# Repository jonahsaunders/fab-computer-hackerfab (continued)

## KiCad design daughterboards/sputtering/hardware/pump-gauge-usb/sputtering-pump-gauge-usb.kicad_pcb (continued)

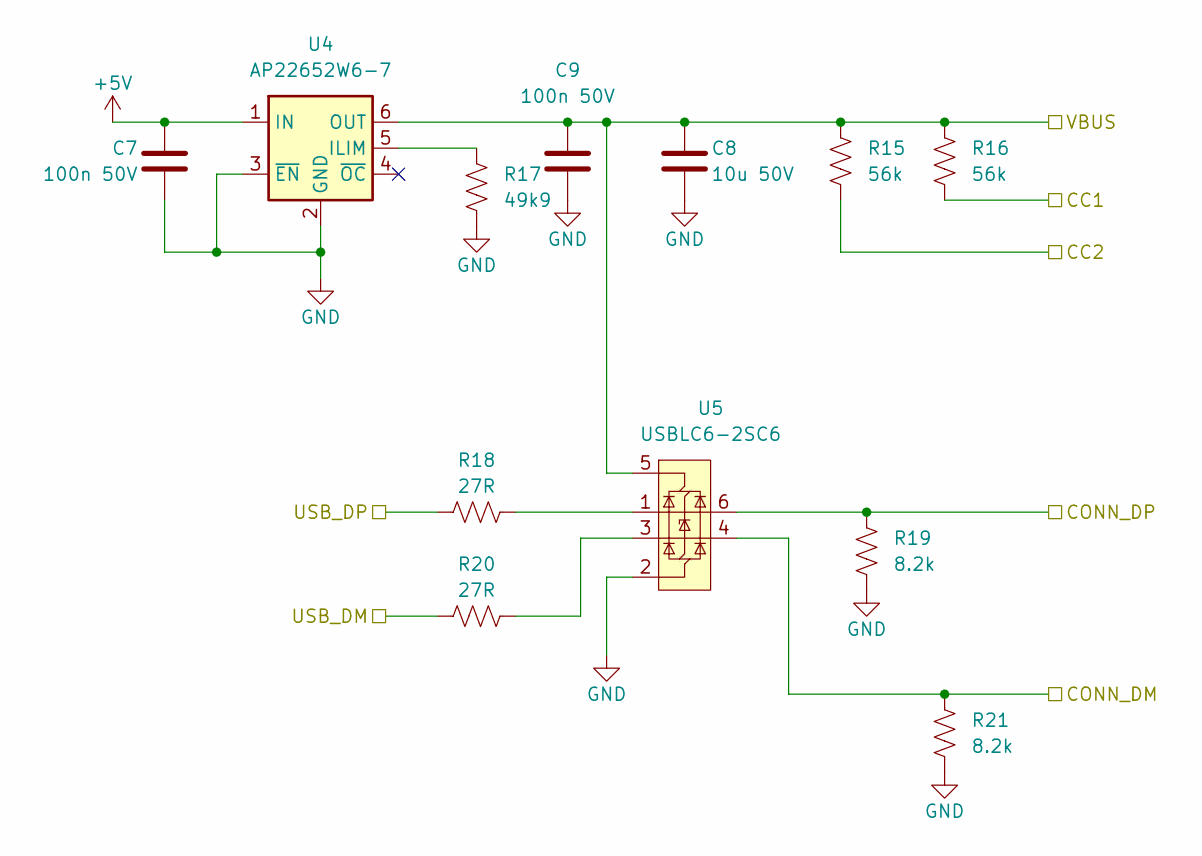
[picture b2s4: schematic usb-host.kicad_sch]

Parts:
C7, C9: 100n 50V; C_0402_1005Metric; LCSC C307331
C8: 10u 50V; C_1206_3216Metric; LCSC C13585
R15, R16: 56k; R_0603_1608Metric; MPN UNI-ROYAL 0603WAF5602T5E; LCSC C23206
R17: 49k9; R_0603_1608Metric; MPN UNI-ROYAL 0603WAF4992T5E; LCSC C23184
R18, R20: 27R; R_0402_1005Metric; LCSC C25100
R19, R21: 8.2k; R_0603_1608Metric; MPN UNI-ROYAL 0603WAF8201T5E; LCSC C25981
U4: AP22652W6-7; SOT-23-6; MPN Diodes AP22652W6-7; LCSC C2158038
U5: USBLC6-2SC6; SOT-23-6; LCSC C7519

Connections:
+5V: C7.1, U4.1 (IN); also elsewhere on the board
/USB_DM: R20.1; also elsewhere on the board
/USB_DP: R18.1; also elsewhere on the board
/usb-host/CC1: R16.2; also elsewhere on the board
/usb-host/CC2: R15.2; also elsewhere on the board
/usb-host/CONN_DM: R21.1, U5.4 (I/O2); also elsewhere on the board
/usb-host/CONN_DP: R19.1, U5.6 (I/O1); also elsewhere on the board
/usb-host/VBUS: C8.1, C9.1, R15.1, R16.1, U4.6 (OUT), U5.5 (VBUS); also elsewhere on the board
GND: C7.2, C8.2, C9.2, R17.2, R19.2, R21.2, U4.2 (GND), U4.3 (~EN), U5.2 (GND); also elsewhere on the board
unnamed: R18.2, U5.1 (I/O1)
unnamed: R20.2, U5.3 (I/O2)
unnamed: R17.1, U4.5 (ILIM)

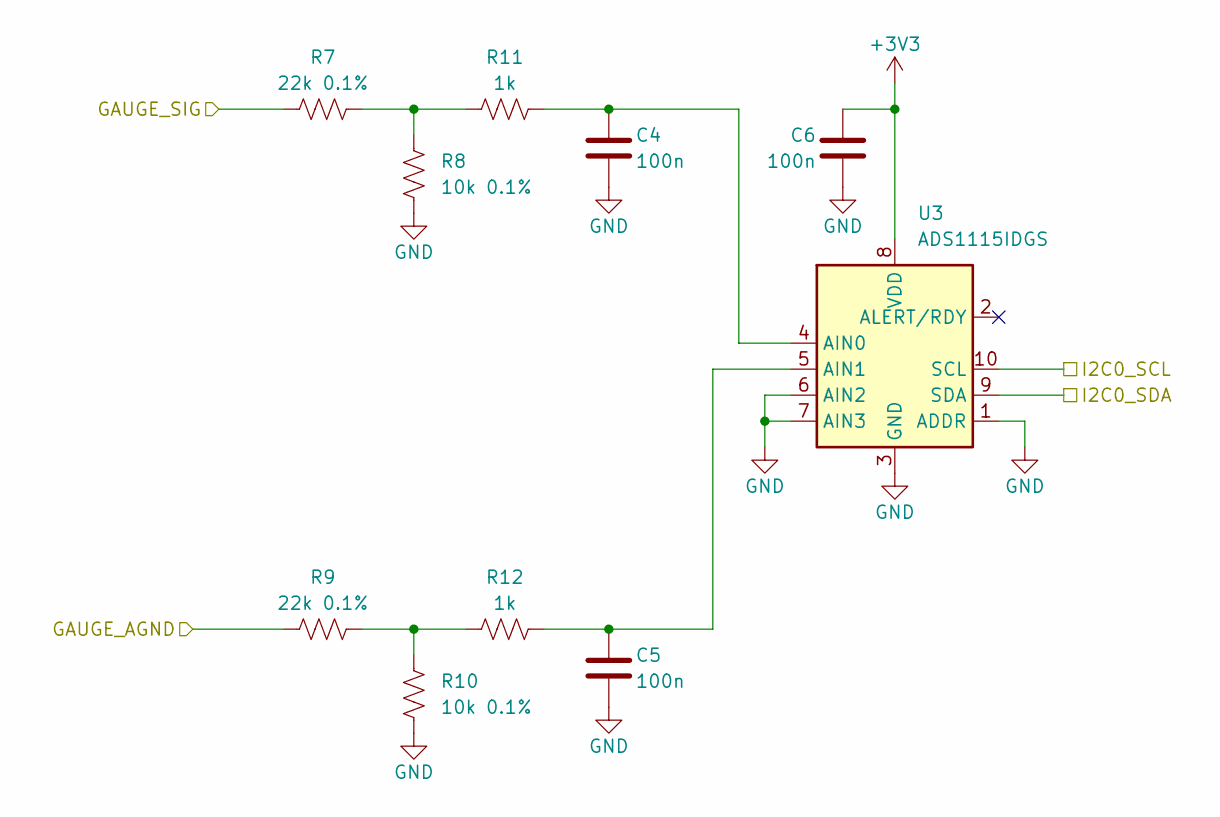
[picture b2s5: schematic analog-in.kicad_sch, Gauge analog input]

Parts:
C4, C5, C6: 100n; C_0402_1005Metric; LCSC C1525
R7, R9: 22k 0.1%; R_0603_1608Metric; MPN Yageo RT0603BRE0722KL; LCSC C705830
R8, R10: 10k 0.1%; R_0603_1608Metric; MPN Yageo RT0603BRE0710KL; LCSC C136139
R11, R12: 1k; R_0603_1608Metric; LCSC C21190
U3: ADS1115IDGS; TSSOP-10_3x3mm_P0.5mm; MPN TI ADS1115IDGSR; LCSC C37593

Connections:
+3V3: C6.1, U3.8 (VDD); also elsewhere on the board
/I2C0_SCL: U3.10 (SCL); also elsewhere on the board
/I2C0_SDA: U3.9 (SDA); also elsewhere on the board
/analog-in/GAUGE_AGND: R9.1; also elsewhere on the board
/analog-in/GAUGE_SIG: R7.1; also elsewhere on the board
GND: C4.2, C5.2, C6.2, R8.2, R10.2, U3.1 (ADDR), U3.3 (GND), U3.6 (AIN2), U3.7 (AIN3); also elsewhere on the board
unnamed: R9.2, R10.1, R12.1
unnamed: R7.2, R8.1, R11.1
unnamed: C4.1, R11.2, U3.4 (AIN0)
unnamed: C5.1, R12.2, U3.5 (AIN1)

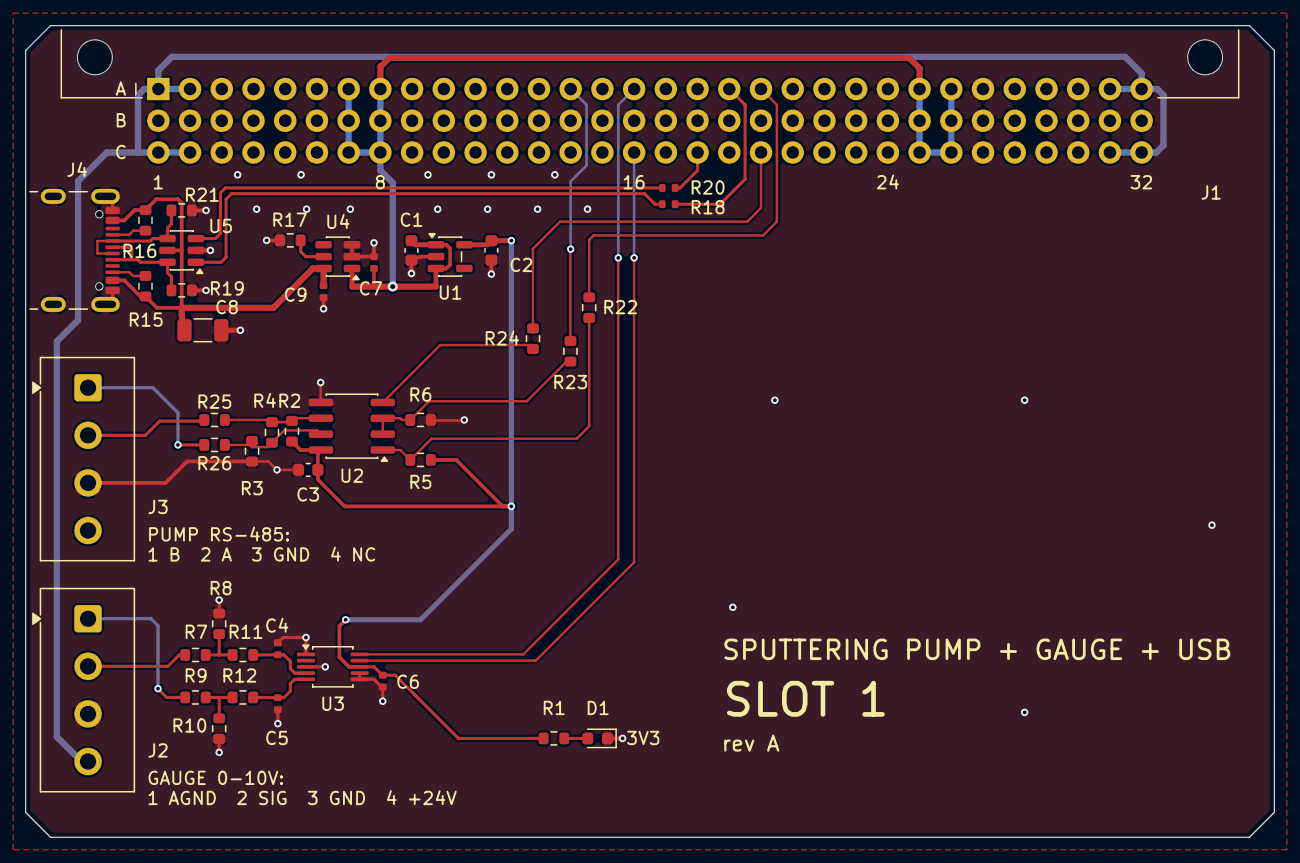
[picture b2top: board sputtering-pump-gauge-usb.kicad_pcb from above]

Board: 2 copper layers, 100.0 x 65.0 mm, 43 parts (0 on the bottom side), 33 nets.

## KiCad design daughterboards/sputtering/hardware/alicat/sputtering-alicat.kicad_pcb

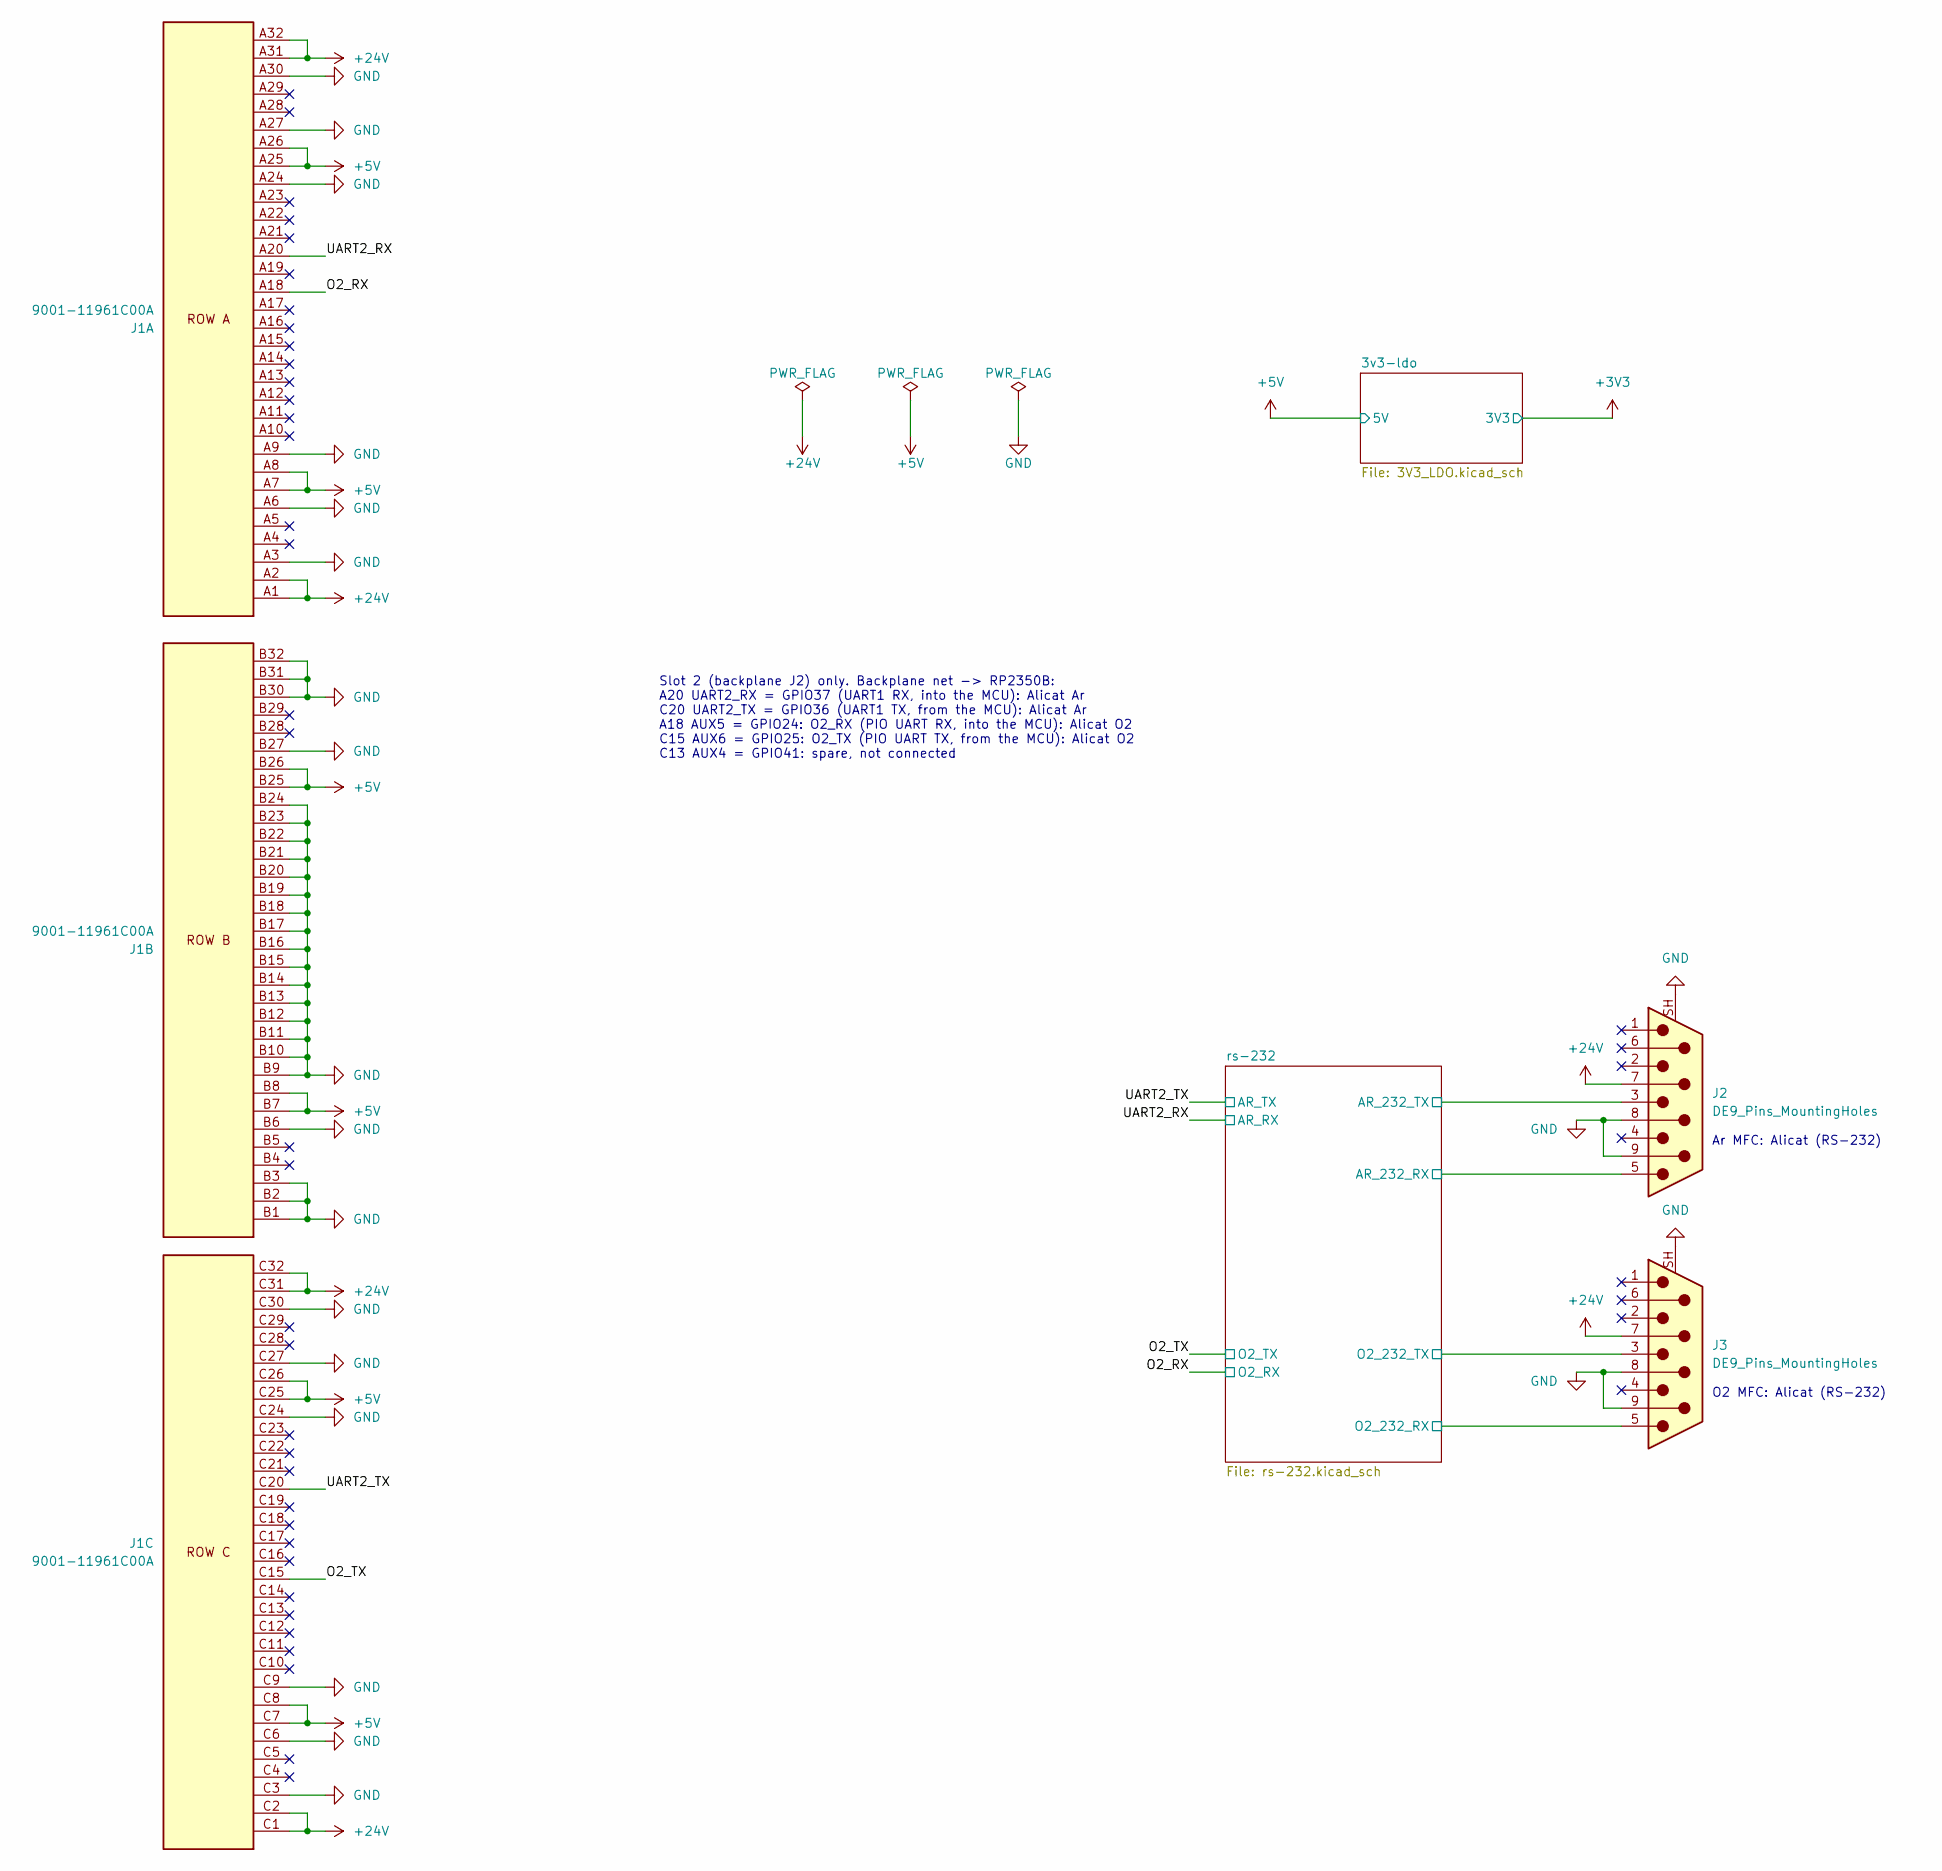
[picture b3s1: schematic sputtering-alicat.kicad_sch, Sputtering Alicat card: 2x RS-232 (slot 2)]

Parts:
J1: 9001-11961C00A; WingTAT_9001-11961C00A_DIN41612_C_3x32_RightAngle; LCSC C5173361
J2, J3: DE9_Pins_MountingHoles; DSUB-9_Pins_Horizontal_P2.77x2.84mm_EdgePinOffset7.70mm_Hou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; MPN CONNFLY DS1037-09MNAKT74-0CC; LCSC C75750

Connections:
+5V: J1.A7, J1.A8, J1.A25, J1.A26, J1.B7, J1.B8, J1.B25, J1.B26, J1.C7, J1.C8, J1.C25, J1.C26; also elsewhere on the board
+24V: J1.A1, J1.A2, J1.A31, J1.A32, J1.C1, J1.C2, J1.C31, J1.C32, J2.7, J3.7
/O2_RX: J1.A18; also elsewhere on the board
/O2_TX: J1.C15; also elsewhere on the board
/UART2_RX: J1.A20; also elsewhere on the board
/UART2_TX: J1.C20; also elsewhere on the board
/rs-232/AR_232_RX: J2.5; also elsewhere on the board
/rs-232/AR_232_TX: J2.3; also elsewhere on the board
/rs-232/O2_232_RX: J3.5; also elsewhere on the board
/rs-232/O2_232_TX: J3.3; also elsewhere on the board
GND: J1.A3, J1.A6, J1.A9, J1.A24, J1.A27, J1.A30, J1.B1, J1.B2, J1.B3, J1.B6, J1.B9, J1.B10, J1.B11, J1.B12, J1.B13, J1.B14, J1.B15, J1.B16, J1.B17, J1.B18, J1.B19, J1.B20, J1.B21, J1.B22, J1.B23, J1.B24, J1.B27, J1.B30, J1.B31, J1.B32, J1.C3, J1.C6, J1.C9, J1.C24, J1.C27, J1.C30, J2.8, J2.9, J2.SH (PAD), J3.8, J3.9, J3.SH (PAD); also elsewhere on the board

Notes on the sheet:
Ar MFC: Alicat (RS-232)
Slot 2 (backplane J2) only. Backplane net -> RP2350B: A20 UART2_RX = GPIO37 (UART1 RX, into the MCU): Alicat Ar C20 UART2_TX = GPIO36 (UART1 TX, from the MCU): Alicat Ar A18 AUX5 = GPIO24: O2_RX (PIO UART RX, into the MCU): Alicat O2 C15 AUX6 = GPIO25: O2_TX (PIO UART TX, from the MCU): Alicat O2 C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
O2 MFC: Alicat (RS-232)

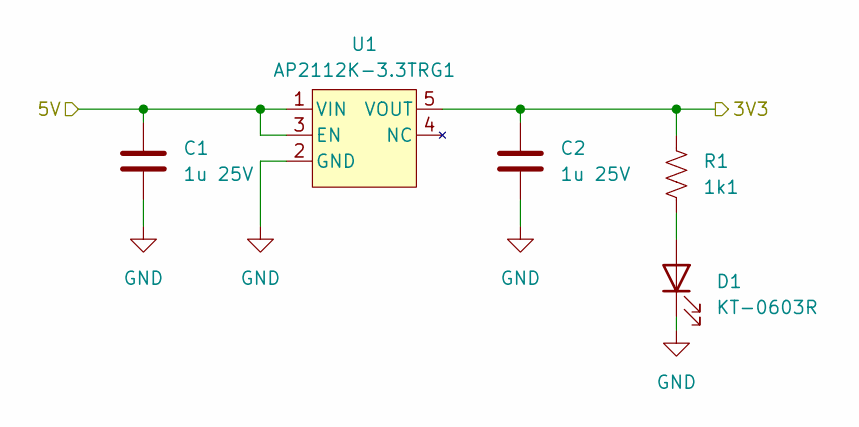
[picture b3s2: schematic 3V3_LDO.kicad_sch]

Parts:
C1, C2: 1u 25V; C_0603_1608Metric; LCSC C15849
D1: KT-0603R; LED_0603_1608Metric; MPN KT-0603R; LCSC C2286
R1: 1k1; R_0603_1608Metric; LCSC C22764
U1: AP2112K-3.3TRG1; SOT-23-5; LCSC C51118

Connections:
+3V3: C2.1, R1.1, U1.5 (VOUT); also elsewhere on the board
+5V: C1.1, U1.1 (VIN), U1.3 (EN); also elsewhere on the board
GND: C1.2, C2.2, D1.1 (K), U1.2 (GND); also elsewhere on the board
unnamed: D1.2 (A), R1.2

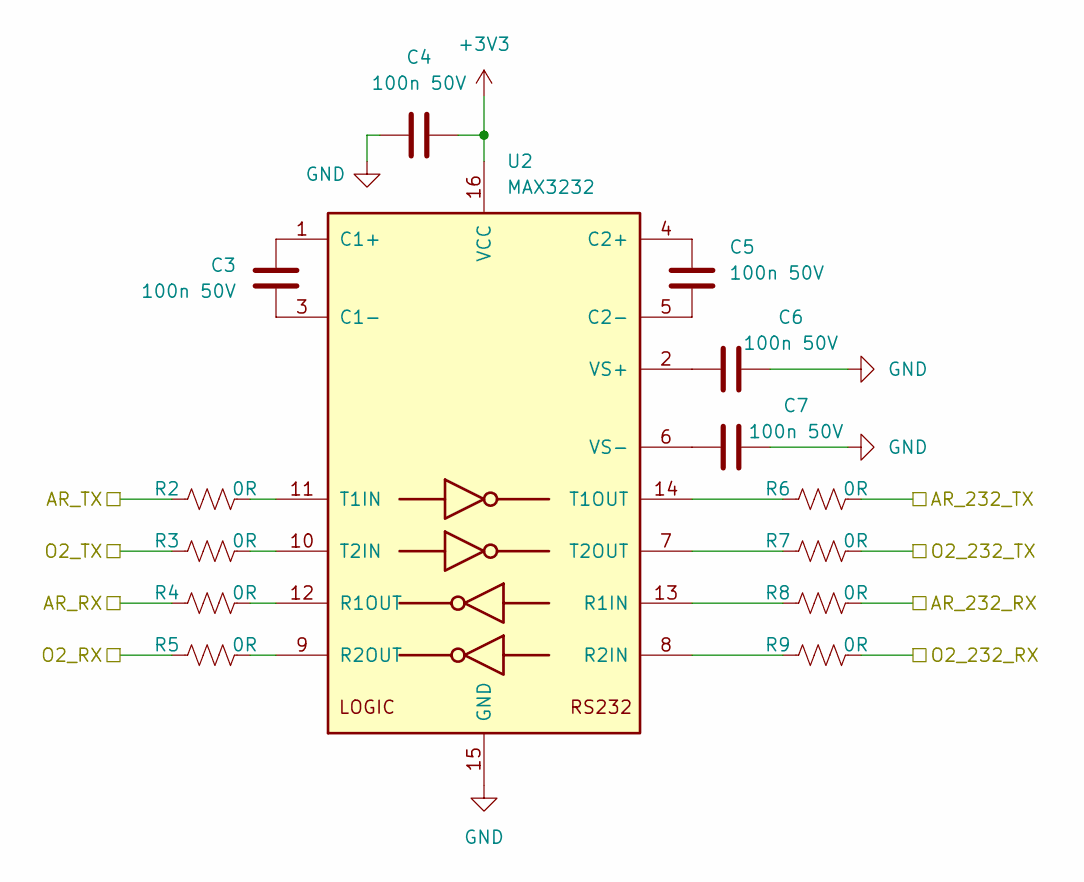
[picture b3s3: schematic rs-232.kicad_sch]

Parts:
C3, C4, C5, C6, C7: 100n 50V; C_0402_1005Metric; LCSC C307331
R2, R3, R4, R5, R6, R7, R8, R9: 0R; R_0603_1608Metric; LCSC C21189
U2: MAX3232; SOIC-16_3.9x9.9mm_P1.27mm; MPN Maxim MAX3232ESE+T; LCSC C15846

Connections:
+3V3: C4.1, U2.16 (VCC); also elsewhere on the board
/O2_RX: R5.1; also elsewhere on the board
/O2_TX: R3.1; also elsewhere on the board
/UART2_RX: R4.1; also elsewhere on the board
/UART2_TX: R2.1; also elsewhere on the board
/rs-232/AR_232_RX: R8.2; also elsewhere on the board
/rs-232/AR_232_TX: R6.2; also elsewhere on the board
/rs-232/O2_232_RX: R9.2; also elsewhere on the board
/rs-232/O2_232_TX: R7.2; also elsewhere on the board
GND: C4.2, C6.1, C7.1, U2.15 (GND); also elsewhere on the board
unnamed: C3.2, U2.1 (C1+)
unnamed: C3.1, U2.3 (C1-)
unnamed: C5.2, U2.4 (C2+)
unnamed: C5.1, U2.5 (C2-)
unnamed: R8.1, U2.13 (R1IN)
unnamed: R4.2, U2.12 (R1OUT)
unnamed: R9.1, U2.8 (R2IN)
unnamed: R5.2, U2.9 (R2OUT)
unnamed: R2.2, U2.11 (T1IN)
unnamed: R6.1, U2.14 (T1OUT)
unnamed: R3.2, U2.10 (T2IN)
unnamed: R7.1, U2.7 (T2OUT)
unnamed: C6.2, U2.2 (VS+)
unnamed: C7.2, U2.6 (VS-)

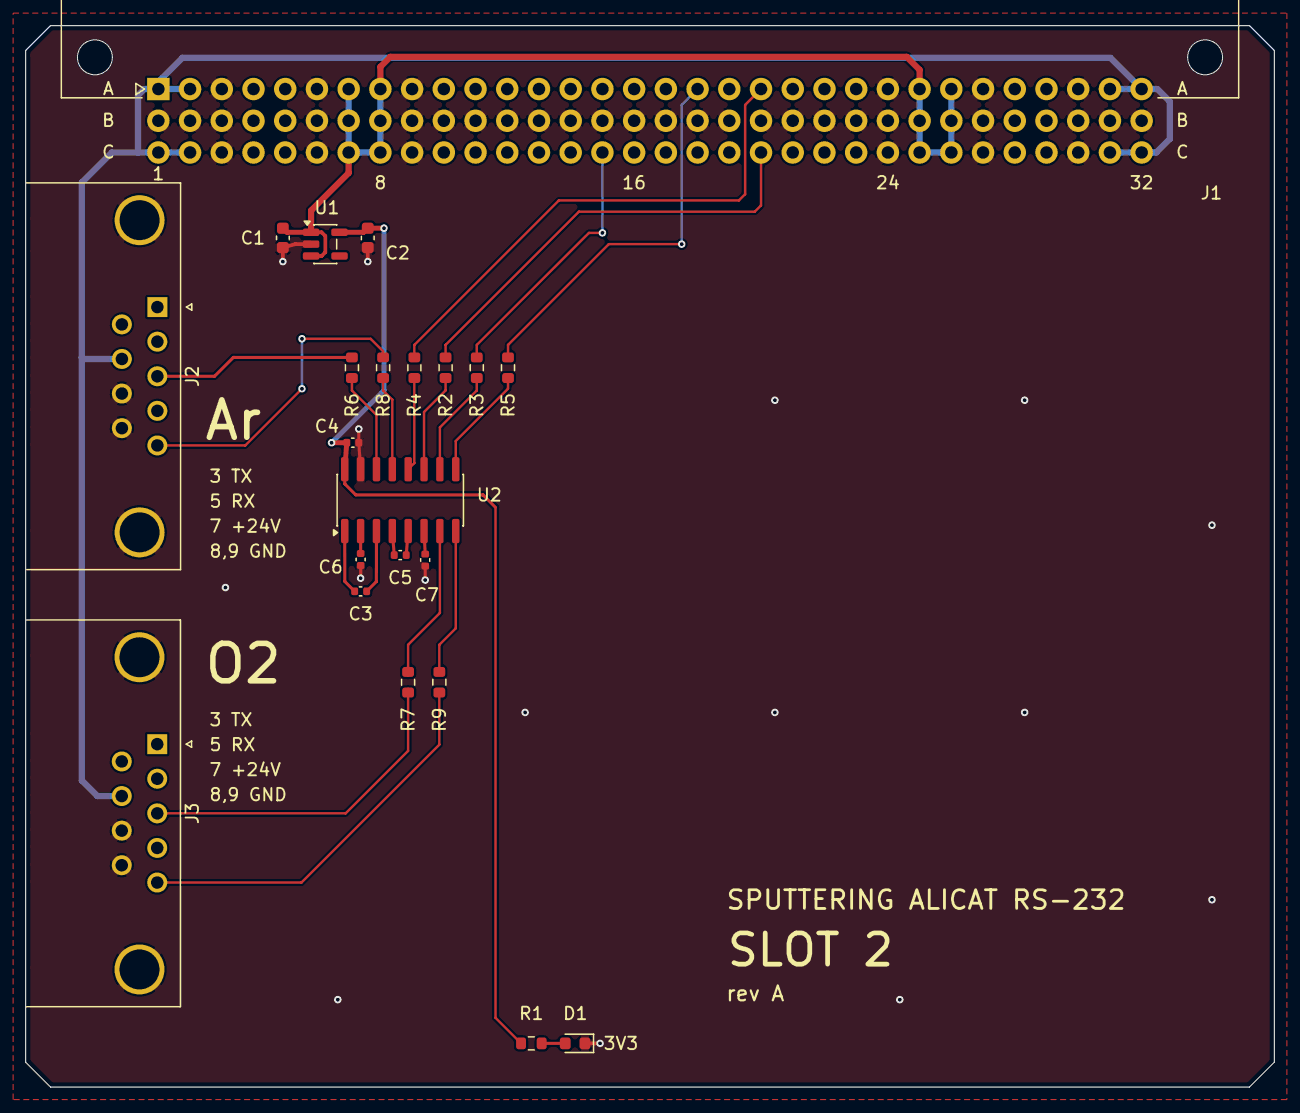
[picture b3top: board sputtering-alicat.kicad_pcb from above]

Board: 2 copper layers, 100.0 x 85.0 mm, 22 parts (0 on the bottom side), 27 nets.

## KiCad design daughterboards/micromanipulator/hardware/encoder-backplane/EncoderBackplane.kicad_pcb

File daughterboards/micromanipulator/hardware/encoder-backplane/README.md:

# Slot-mounted encoder splitter

Open [EncoderBackplane.kicad_pro](EncoderBackplane.kicad_pro) in KiCad 10. This **100 × 26 mm, four-layer** card plugs into an unused backplane slot and connects three existing XYZ magnetic-encoder boards. Keep the sibling `libraries` directory with it.

The motion card reads the encoders through the existing shared SPI0 bus. The host CPU must leave GPIO16–21 as inputs without pulls; SPI0 and all three selects are reserved for this pair. The host board is unchanged. See the [bus map and requirements](../../docs/backplane-encoder-bus.md).

J1/J2/J3 are JST B6B-PH-K-S(LF)(SN), **LCSC C131342**, matching the original PH6 sensor wiring: 1 GND, 2 CS, 3 SCK, 4 MOSI, 5 MISO, 6 3.3 V. Top-entry plugs project from the component face; the connectors sit at the exposed edge. Local KiCad models show their direction and nominal bodies.

J4 is the same DIN96 male right-angle interface as the motion card. An AP2112M-3.3 uses backplane 5 V; no extra contact or development module is used. TP1/TP2 probe 5 V/3.3 V, with TP3/TP4 grounds. All are 0.8 mm surface copper pads without holes or paste. Eleven fitted parts plus four bare probe pads.

[Schematic PDF](../../docs/encoder-backplane-schematic.pdf) · [3D view](../../docs/encoder-backplane.png) · [BOM](../../docs/encoder-backplane-bom.csv) · [Validation](../../docs/validation.md)

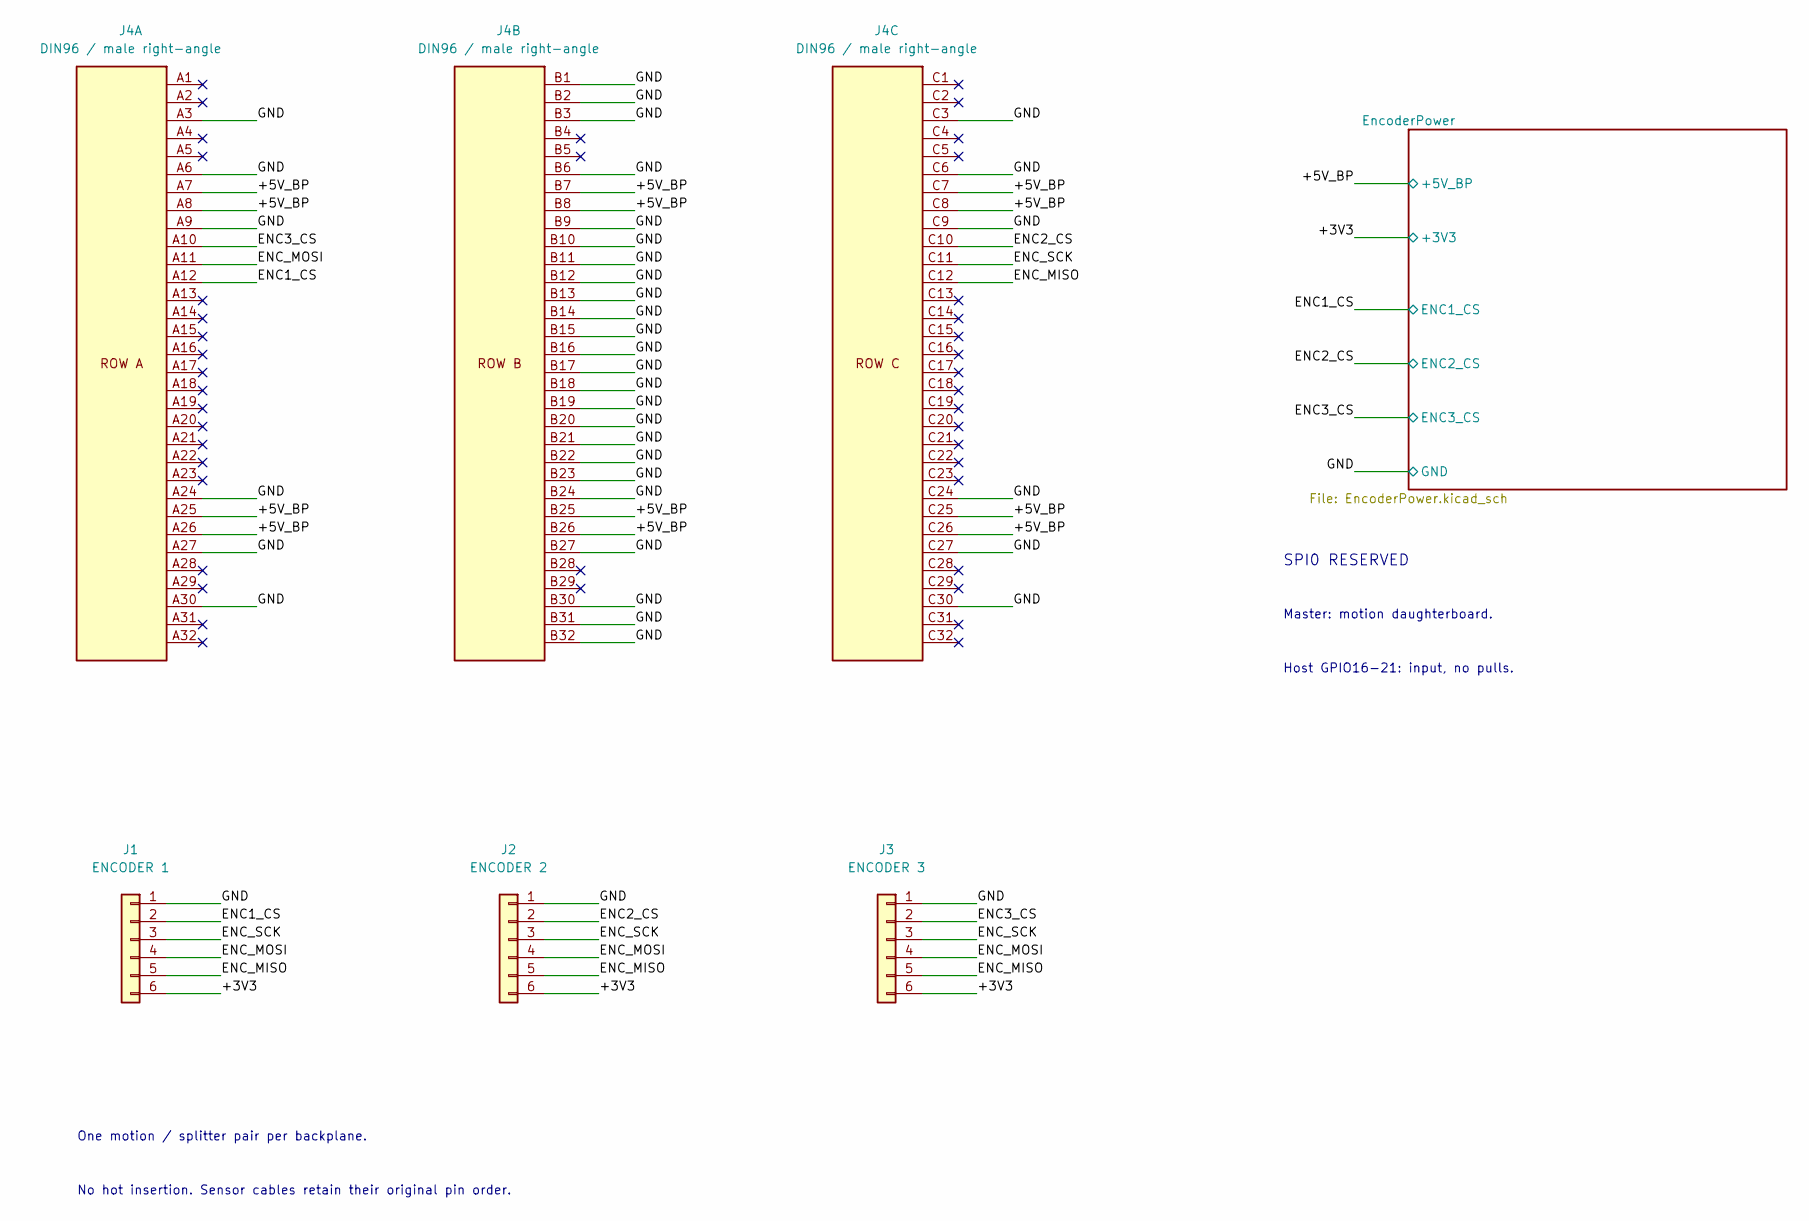
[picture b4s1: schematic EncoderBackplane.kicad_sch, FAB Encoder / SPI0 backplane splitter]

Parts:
J1: ENCODER 1; JST_PH_B6B-PH-K_1x06_P2.00mm_Vertical; MPN B6B-PH-K-S(LF)(SN); LCSC C131342
J2: ENCODER 2; JST_PH_B6B-PH-K_1x06_P2.00mm_Vertical; MPN B6B-PH-K-S(LF)(SN); LCSC C131342
J3: ENCODER 3; JST_PH_B6B-PH-K_1x06_P2.00mm_Vertical; MPN B6B-PH-K-S(LF)(SN); LCSC C131342
J4: DIN96 / male right-angle; DIN96_Male_Horizontal; MPN 9001-11961C00A; LCSC C5173361

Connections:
+3V3: J1.6, J2.6, J3.6; also elsewhere on the board
+5V_BP: J4.A7, J4.A8, J4.A25, J4.A26, J4.B7, J4.B8, J4.B25, J4.B26, J4.C7, J4.C8, J4.C25, J4.C26; also elsewhere on the board
/ENC1_CS: J1.2, J4.A12; also elsewhere on the board
/ENC2_CS: J2.2, J4.C10; also elsewhere on the board
/ENC3_CS: J3.2, J4.A10; also elsewhere on the board
/ENC_MISO: J1.5, J2.5, J3.5, J4.C12
/ENC_MOSI: J1.4, J2.4, J3.4, J4.A11
/ENC_SCK: J1.3, J2.3, J3.3, J4.C11
GND: J1.1, J2.1, J3.1, J4.A3, J4.A6, J4.A9, J4.A24, J4.A27, J4.A30, J4.B1, J4.B2, J4.B3, J4.B6, J4.B9, J4.B10, J4.B11, J4.B12, J4.B13, J4.B14, J4.B15, J4.B16, J4.B17, J4.B18, J4.B19, J4.B20, J4.B21, J4.B22, J4.B23, J4.B24, J4.B27, J4.B30, J4.B31, J4.B32, J4.C3, J4.C6, J4.C9, J4.C24, J4.C27, J4.C30; also elsewhere on the board

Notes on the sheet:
SPI0 RESERVED
Master: motion daughterboard.
Host GPIO16-21: input, no pulls.
One motion / splitter pair per backplane.
No hot insertion. Sensor cables retain their original pin order.

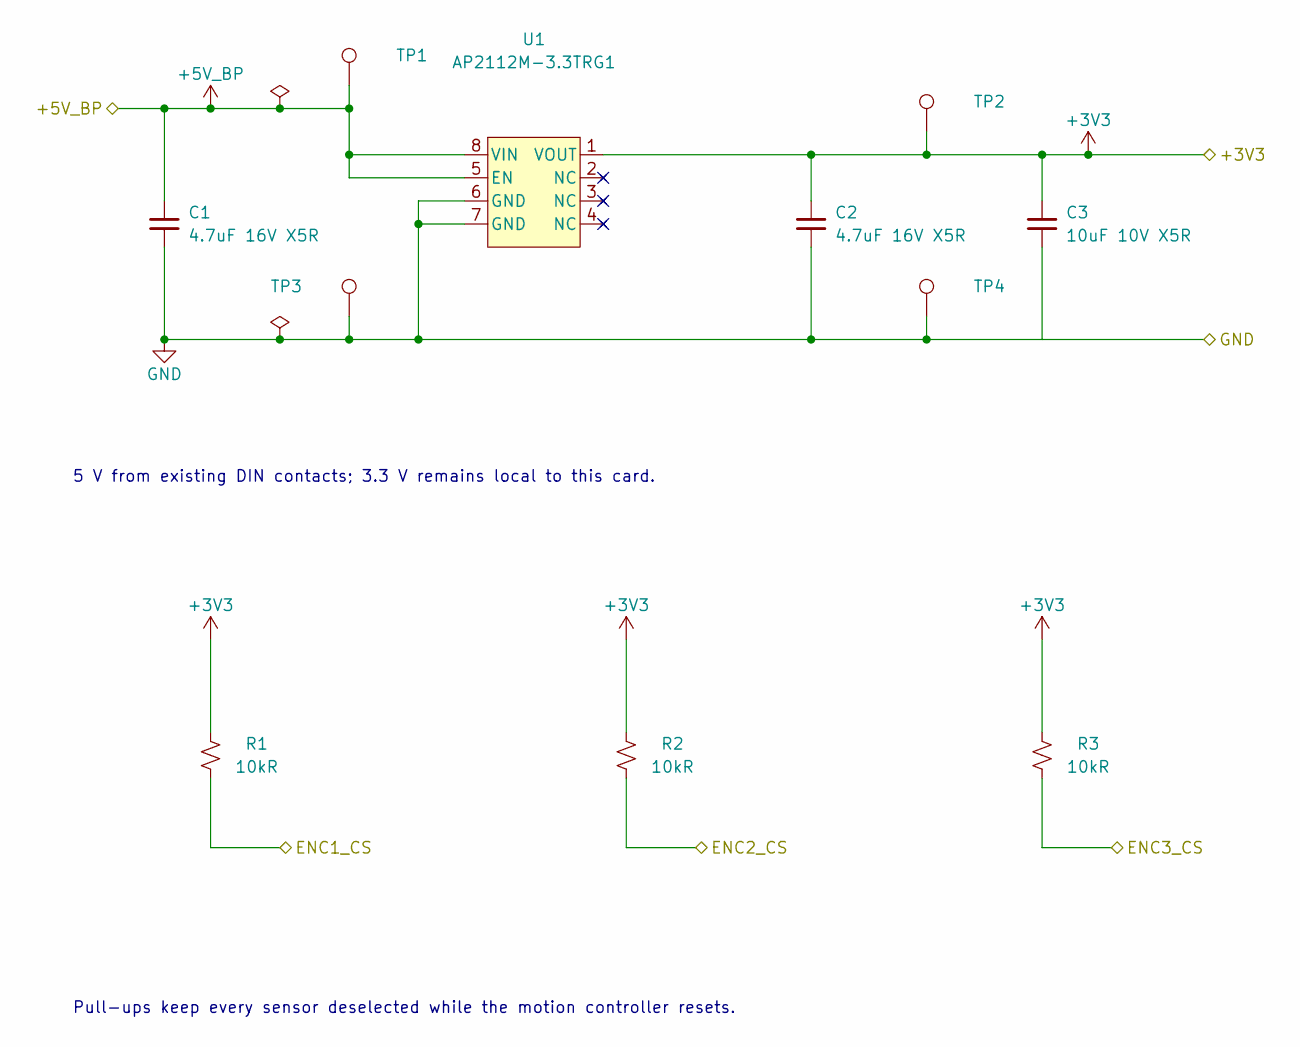
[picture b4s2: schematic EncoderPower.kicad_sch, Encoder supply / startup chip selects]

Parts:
C1, C2: 4.7uF 16V X5R; C_0603_1608Metric; MPN CL10A475KO8NNNC; LCSC C19666
C3: 10uF 10V X5R; C_0603_1608Metric; MPN CL10A106KP8NNNC; LCSC C19702
R1, R2, R3: 10kR; R_0603_1608Metric; MPN 0603WAF1002T5E; LCSC C25804
TP1: 5V; TestPoint_Pad_D0.8mm
TP2: 3V3; TestPoint_Pad_D0.8mm
TP3, TP4: GND; TestPoint_Pad_D0.8mm
U1: AP2112M-3.3TRG1; SOIC-8_3.9x4.9mm_P1.27mm; MPN AP2112M-3.3TRG1; LCSC C5290219

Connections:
+3V3: C2.1, C3.1, R1.2, R2.2, R3.2, TP2.1, U1.1 (VOUT); also elsewhere on the board
+5V_BP: C1.1, TP1.1, U1.5 (EN), U1.8 (VIN); also elsewhere on the board
/ENC1_CS: R1.1; also elsewhere on the board
/ENC2_CS: R2.1; also elsewhere on the board
/ENC3_CS: R3.1; also elsewhere on the board
GND: C1.2, C2.2, C3.2, TP3.1, TP4.1, U1.6 (GND), U1.7 (GND); also elsewhere on the board

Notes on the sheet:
5 V from existing DIN contacts; 3.3 V remains local to this card.
Pull-ups keep every sensor deselected while the motion controller resets.

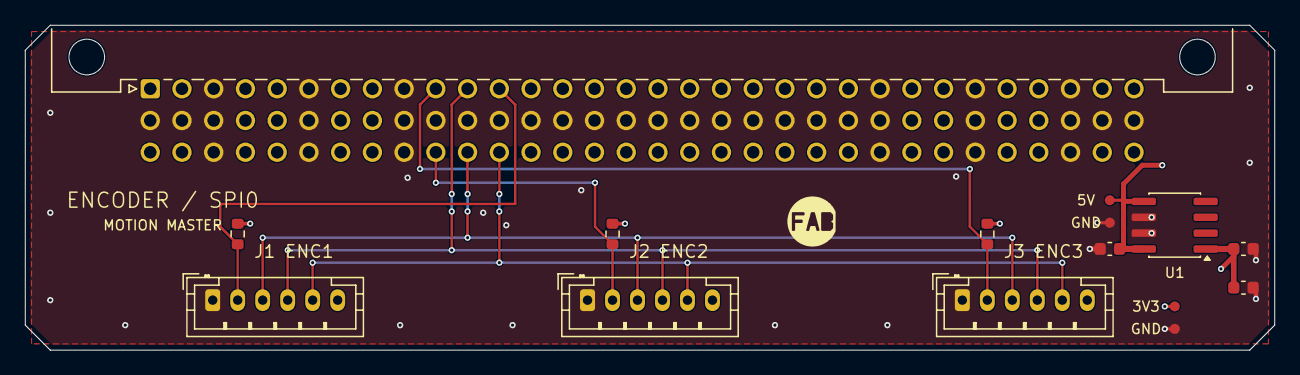
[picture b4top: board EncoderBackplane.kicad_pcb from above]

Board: 4 copper layers, 100.0 x 26.0 mm, 15 parts (0 on the bottom side), 9 nets.

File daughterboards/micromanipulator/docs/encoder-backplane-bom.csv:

Reference,Value,Footprint,Manufacturer part number,Manufacturer,LCSC,Quantity,Procurement status
J1,ENCODER 1,Connector_JST:JST_PH_B6B-PH-K_1x06_P2.00mm_Vertical,B6B-PH-K-S(LF)(SN),JST,C131342,1,Catalog part identified; confirm assembly availability when ordering
J2,ENCODER 2,Connector_JST:JST_PH_B6B-PH-K_1x06_P2.00mm_Vertical,B6B-PH-K-S(LF)(SN),JST,C131342,1,Catalog part identified; confirm assembly availability when ordering
J3,ENCODER 3,Connector_JST:JST_PH_B6B-PH-K_1x06_P2.00mm_Vertical,B6B-PH-K-S(LF)(SN),JST,C131342,1,Catalog part identified; confirm assembly availability when ordering
J4,DIN96 / male right-angle,FabNano:DIN96_Male_Horizontal,9001-11961C00A,WingTAT,C5173361,1,Catalog part identified; confirm assembly availability when ordering
C1,4.7uF 16V X5R,Capacitor_SMD:C_0603_1608Metric,CL10A475KO8NNNC,Samsung Electro-Mechanics,C19666,1,Catalog part identified; confirm assembly availability when ordering
C2,4.7uF 16V X5R,Capacitor_SMD:C_0603_1608Metric,CL10A475KO8NNNC,Samsung Electro-Mechanics,C19666,1,Catalog part identified; confirm assembly availability when ordering
C3,10uF 10V X5R,Capacitor_SMD:C_0603_1608Metric,CL10A106KP8NNNC,Samsung Electro-Mechanics,C19702,1,Catalog part identified; confirm assembly availability when ordering
R1,10kR,Resistor_SMD:R_0603_1608Metric,0603WAF1002T5E,Uniroyal Electronics,C25804,1,Catalog part identified; confirm assembly availability when ordering
R2,10kR,Resistor_SMD:R_0603_1608Metric,0603WAF1002T5E,Uniroyal Electronics,C25804,1,Catalog part identified; confirm assembly availability when ordering
R3,10kR,Resistor_SMD:R_0603_1608Metric,0603WAF1002T5E,Uniroyal Electronics,C25804,1,Catalog part identified; confirm assembly availability when ordering
U1,AP2112M-3.3TRG1,Package_SO:SOIC-8_3.9x4.9mm_P1.27mm,AP2112M-3.3TRG1,Diodes Incorporated,C5290219,1,Catalog part identified; confirm assembly availability when ordering

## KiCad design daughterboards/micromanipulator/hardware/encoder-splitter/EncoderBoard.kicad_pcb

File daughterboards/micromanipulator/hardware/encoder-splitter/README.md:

# Original splitter — source reference only

The active design is now the [slot-mounted encoder card](../encoder-backplane/). This original 36 × 36 mm PH8-to-three-PH6 project is retained for provenance and sensor pinout comparison. Its PH8 connector is not used by the current motion card, which no longer has J6.

# Original XYZ SPI splitter

Open `EncoderBoard.kicad_pro` in KiCad 10. This is HackerFab's existing 36 × 36 mm passive breakout: one PH8 input (J4) and three PH6 outputs (J1–J3). Connect daughterboard J6 to J4 pin-for-pin. The board carries no encoder ICs or development modules.

See the [pin table and import review](../../docs/probe-and-label-review.md#included-original-spi-splitter). Connector positions, pinout, copper and outline are retained from [MicroManipulatorStepper](https://github.com/hacker-fab/MicroManipulatorStepper/tree/fa9a1f8e6d5365c6d5d5f31054d4f2c95aff8f6a/electronics). Models and footprints resolve within the micromanipulator folder. KiCad's standard symbol libraries are used for editing; the schematic contains its cached symbols.

Only local library/model paths, empty datasheet metadata, the daughterboard J6 caption and ERC annotations were normalized. Both ERC and DRC/parity pass. Mounting pads remain electrically isolated as upstream. The original DIYLC distribution drawing is included alongside the KiCad files. Attribution and terms are in [the retained MIT license](../../licenses/MicroManipulatorStepper-MIT.txt).

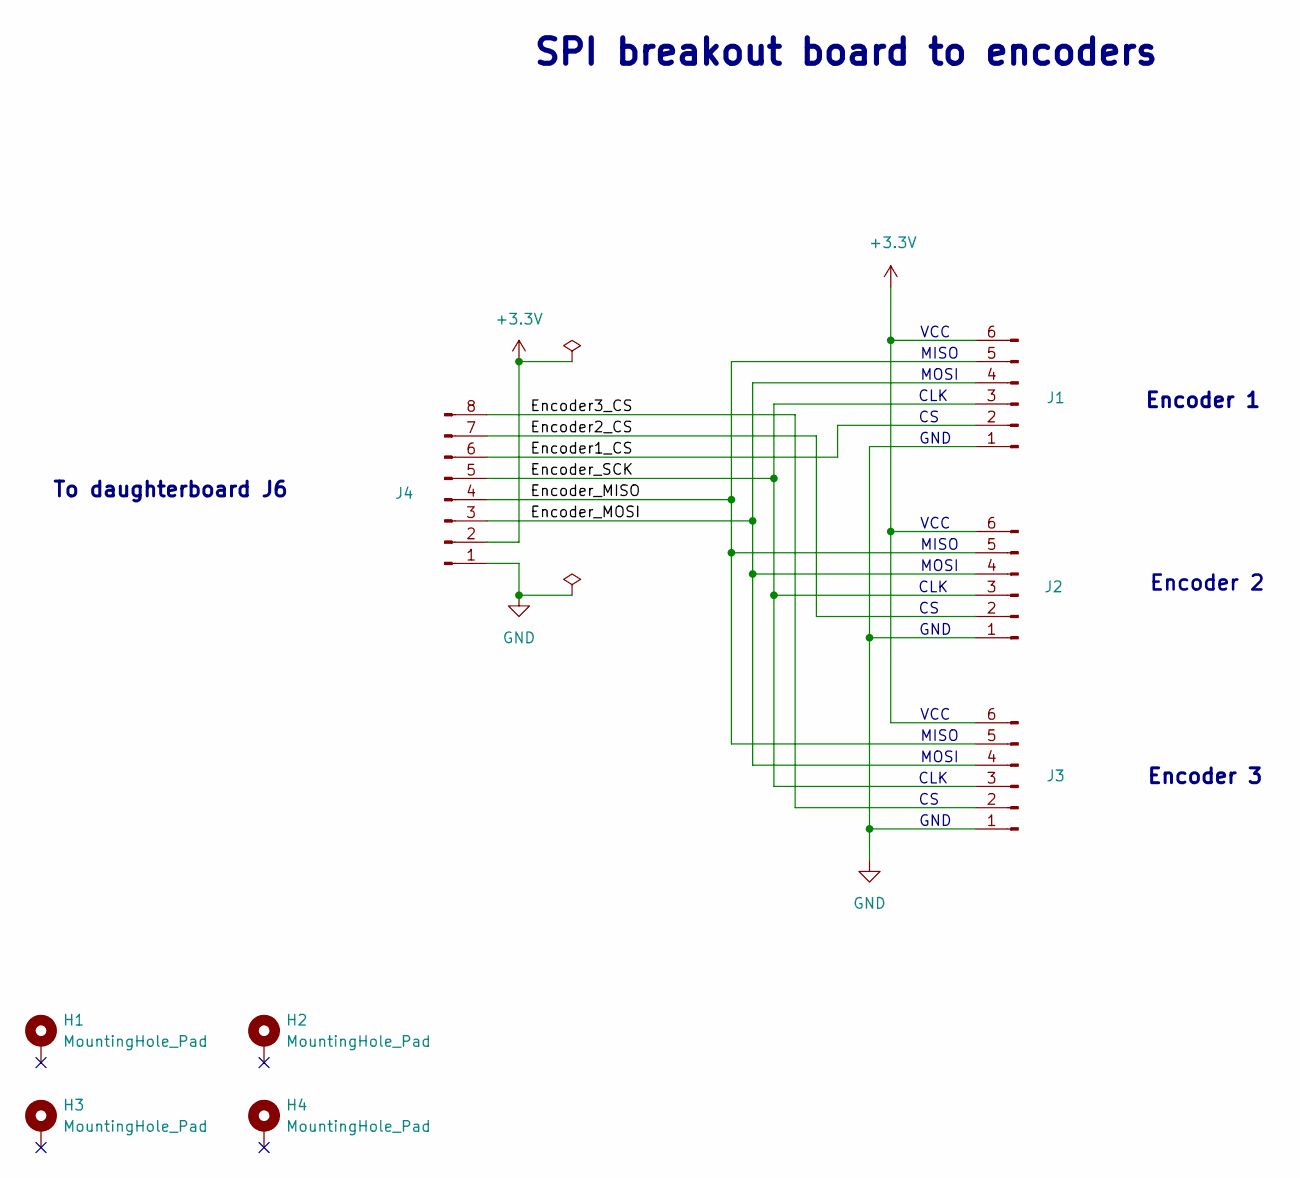
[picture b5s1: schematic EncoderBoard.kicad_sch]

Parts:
H1, H2, H3, H4: MountingHole_Pad; MountingHole_2.7mm_M2.5_Pad_Via
J1, J2, J3: Conn_01x06_Pin; JST_PH_B6B-PH-K_1x06_P2.00mm_Vertical
J4: Conn_01x08_Pin; JST_PH_B8B-PH-K_1x08_P2.00mm_Vertical

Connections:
+3.3V: J1.6, J2.6, J3.6, J4.2
/Encoder1_CS: J1.2, J4.6
/Encoder2_CS: J2.2, J4.7
/Encoder3_CS: J3.2, J4.8
/Encoder_MISO: J1.5, J2.5, J3.5, J4.4
/Encoder_MOSI: J1.4, J2.4, J3.4, J4.3
/Encoder_SCK: J1.3, J2.3, J3.3, J4.5
GND: J1.1, J2.1, J3.1, J4.1

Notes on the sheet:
VCC
Encoder 2
CLK
MISO
To daughterboard J6
MOSI
Encoder 3
SPI breakout board to encoders
GND
Encoder 1

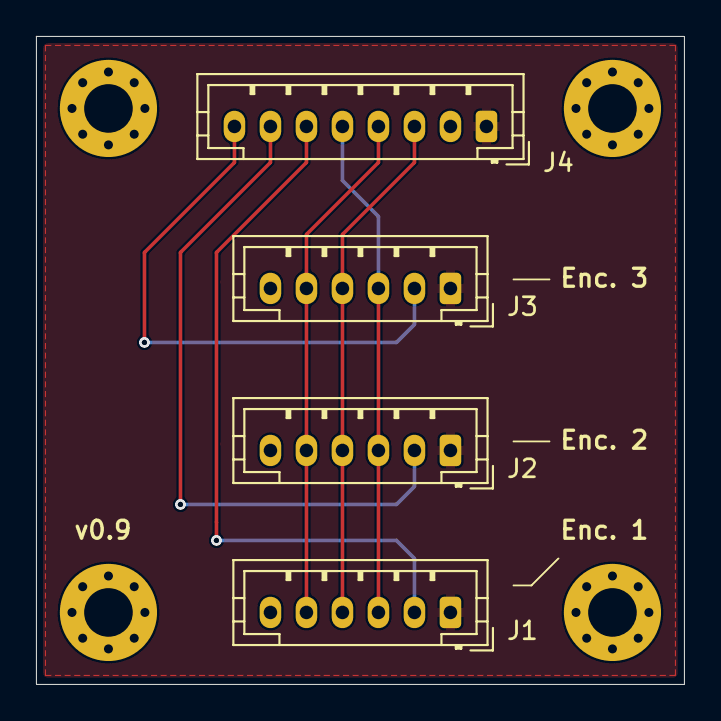
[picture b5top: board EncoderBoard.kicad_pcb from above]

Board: 2 copper layers, 36.0 x 36.0 mm, 8 parts (0 on the bottom side), 8 nets.
